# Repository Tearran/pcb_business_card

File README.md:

# A PCB business card

The Eagle files for a simple PCB business card. Read more about it [here](https://platis.solutions/blog/2015/07/08/pcb-business-card/).

### Preview

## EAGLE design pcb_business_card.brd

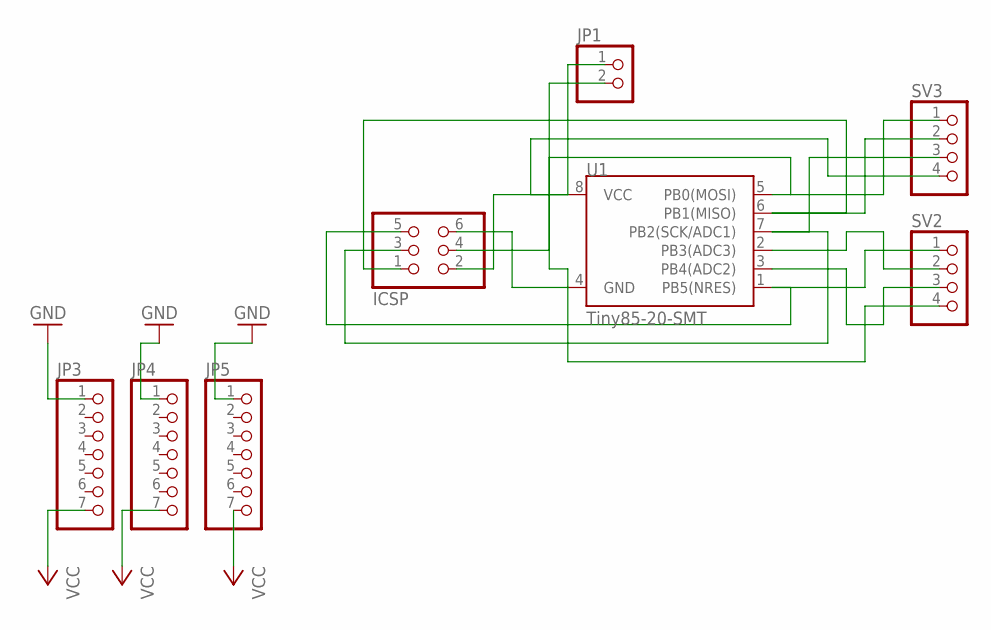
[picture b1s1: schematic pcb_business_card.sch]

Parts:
ICSP: PINHD-2X3; 2X03
JP1: PINHD-1X2; 1X02
JP3, JP4, JP5: PINHD-1X7; 1X07
SV2, SV3: PINHD-1X4; 1X04
U1: Tiny85-20-SMT; SO08-EIAJ

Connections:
GND: ICSP.6, JP1.2, JP3.1, JP4.1, JP5.1, SV2.4, U1.4 (GND)
MISO: ICSP.1, SV3.2, U1.6 (PB1(MISO))
MOSI: ICSP.4, SV3.1, U1.5 (PB0(MOSI))
unnamed: SV2.3, U1.3 (PB4(ADC2))
unnamed: SV2.2, U1.2 (PB3(ADC3))
RESET: ICSP.5, SV2.1, U1.1 (PB5(NRES))
SCK: ICSP.3, SV3.3, U1.7 (PB2(SCK/ADC1))
VCC: ICSP.2, JP1.1, JP3.7, JP4.7, JP5.7, SV3.4, U1.8 (VCC)

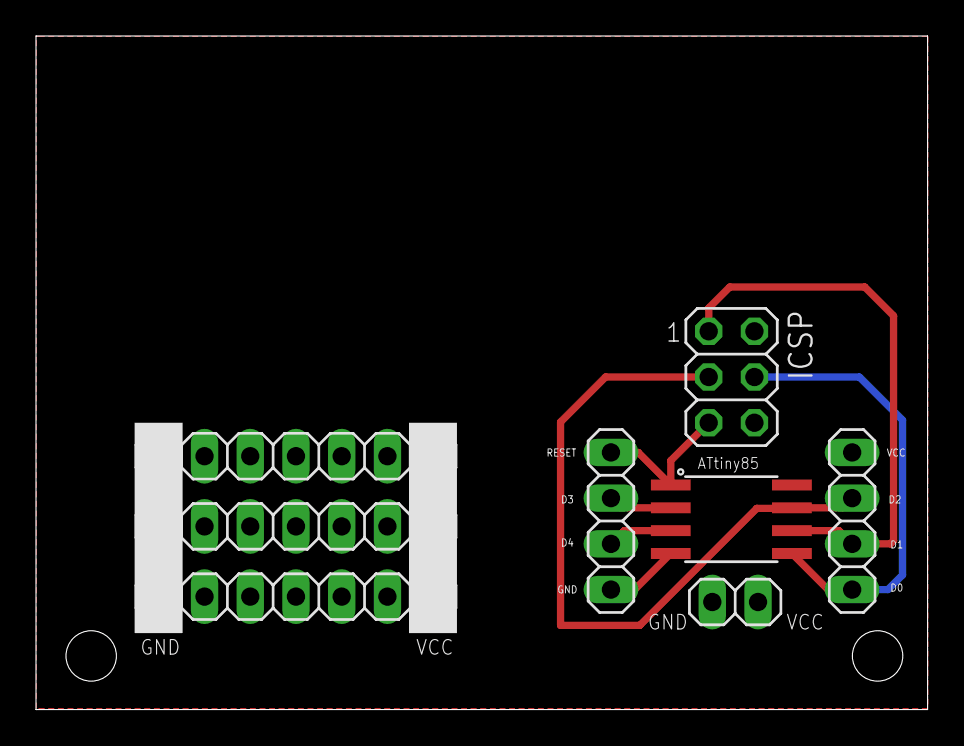
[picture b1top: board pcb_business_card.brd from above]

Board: 2 copper layers, 49.5 x 37.4 mm, 8 parts (0 on the bottom side), 8 nets.

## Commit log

2015-07-08 initial upload
2015-07-08 preview reders from OSH park

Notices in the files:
parts and their libraries:
SparkFun-DigitalIC: Licensing: Creative Commons ShareAlike 4.0 International - https://creativecommons.org/licenses/by-sa/4.0
